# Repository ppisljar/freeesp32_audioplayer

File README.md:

# freeesp32_audioplayer

Open-source ESP32 audio playback board designed primarily as the hardware
platform for [**`freeesp32_ave`**](https://github.com/ppisljar/freeesp32_ave) —
audio-visual entrainment (AVE) firmware.

This repository contains the full **KiCad** project: schematic, PCB layout,
design rules, 3D models, datasheets, and helper scripts.

## Board renders

| Top | Bottom |
|---|---|
|  |  |

*KiCad 3D renders. Top: TRRS headphone jack, USB-C, microSD slot, XIAO ESP32-S3 module, LED/expansion pin headers. Bottom: speaker amplifier (APA2068), bulk capacitors, level-shifting resistors.*

## Board features

- **MCU module**: Seeed Studio **XIAO ESP32-S3** (Wi-Fi + BLE)
- **Headphone output**: Cirrus Logic **CS4344** stereo I²S DAC
- **Speaker output**: **APA2068** Class-D power amplifier
- **Storage**: microSD card slot for offline audio and timeline files
- **LED outputs**: configurable headers — works with NeoPixel (WS2812),
  DotStar (APA102), or direct PWM strips (the firmware picks the backend)

## Power

The board can be powered any of three ways. The 5 V rail feeds the speaker
amplifier (APA2068), and the XIAO's onboard LDO derives the 3.3 V rail
that feeds the DAC (CS4344) and the MCU itself.

| Source | Connector | Voltage | Notes |
|---|---|---|---|
| **USB-C** | XIAO ESP32-S3 onboard | 5 V (USB VBUS) | Also used for flashing firmware and the serial console. The default during development. |
| **External 5 V** | `J4` — JST PH 2-pin (`V+_EXT`) | 5 V regulated | For powering from a bench supply, wall adapter, or upstream USB-PD trigger. |
| **Li-ion battery** | `J5` — JST PH 2-pin (`BATTERY`) | 3.0 – 4.2 V | Connects to the XIAO's `BAT+` pin. The XIAO's built-in charger manages the cell when USB is also plugged in. |

### Battery-powered audio

A single Li-ion cell sits below the 5 V needed by the speaker amplifier,
so the board includes a **TPS61023 synchronous boost converter** (`U4`)
that lifts `BAT+` up to 5 V. Output is fed into the 5 V rail through a
Schottky diode (`D1`) so the boost output can't backfeed USB VBUS when
both USB and battery are connected.

This means the speaker output works on battery just as well as on USB —
no compromise.

### Combining sources — what's safe

| Combination | Safe? | Why |
|---|---|---|
| USB + battery | ✅ Yes | XIAO charges the cell; `D1` blocks the boost from feeding USB. |
| USB + external 5 V (`J4`) | ❌ **No — pick one** | Both feed the 5 V rail directly. Hot-swapping risks back-feeding the upstream supply. |
| External 5 V + battery | ✅ Yes | Same reasoning as USB + battery — `D1` isolates the boost. |

> **Tip**: if you intend to deploy the board untethered in a meditation
> session, leave USB unplugged once you've flashed the firmware. The
> XIAO's USB controller draws current even when the host is idle.

## Repository layout

```
main_board/
├── esp32audio.kicad_sch    # schematic
├── esp32audio.kicad_pcb    # PCB layout
├── esp32audio.kicad_pro    # KiCad project
├── 3dmodels/               # STEP models for enclosure design
├── datasheets/             # IC datasheets and reference schematics
├── analysis/               # generated reports (regenerable from source)
├── images/                 # 3D renders used in this README
├── outputs/                # gerbers, drill files, BOM, pick-and-place CSVs
└── *.py                    # helper scripts (netlist sync, freerouting…)
```

## Related projects

| Repo | Role |
|---|---|
| [`freeesp32_audioplayer`](https://github.com/ppisljar/freeesp32_audioplayer) | **This repo** — open hardware (KiCad) |
| [`freeesp32_ave`](https://github.com/ppisljar/freeesp32_ave) | AVE firmware that runs on this board |
| [`freeesp32_ave_generator`](https://github.com/ppisljar/freeesp32_ave_generator) | Web editor that generates session timelines for the firmware |

## Ordering the board

The `main_board/outputs/` directory contains everything a PCB fab needs:

| File / folder | Purpose |
|---|---|
| `outputs/Archive.zip` | Gerbers + drill file (KiCad standard layer naming) |
| `outputs/esp32audio.csv` | BOM with manufacturer part numbers (MPNs) |
| `outputs/esp32audio-*-pos.csv` | Pick-and-place coordinates (top / bottom / all) |

### PCBWay (recommended for assembly with non-LCSC parts)

1. Go to <https://www.pcbway.com/orderonline.aspx> and upload `outputs/Archive.zip`. The site auto-detects board size, layer count (2-layer), and finish.
2. Defaults are fine: **FR-4, 1.6 mm, HASL or ENIG, green soldermask, white silkscreen**.
3. For assembly: enable **PCB Assembly**, upload `esp32audio.csv` (BOM) and `esp32audio-top-pos.csv` + `esp32audio-bottom-pos.csv` (CPL). PCBWay sources parts by MPN globally — useful if any component is out of stock on LCSC.
4. Quoting + DFM review typically completes within 24 h; bare-board lead time ~3–5 days, assembled ~7–10 days.

### JLCPCB (cheaper for bare boards / parts available on LCSC)

1. Go to <https://cart.jlcpcb.com/quote> and upload `outputs/Archive.zip`.
2. Defaults are fine. JLCPCB's free options match what this design needs.
3. For assembly: enable **PCBA**, upload `esp32audio.csv` (BOM) and `esp32audio-all-pos.csv` (CPL). JLCPCB requires the parts to be in their LCSC catalog — verify MPN availability before ordering, and substitute equivalents in the BOM where needed.

### Bare-board only (any fab)

Just upload `outputs/Archive.zip` — the gerbers use KiCad's standard layer naming (`F_Cu`, `B_Cu`, `F_Mask`, `B_Mask`, `F_Paste`, `B_Paste`, `F_Silkscreen`, `B_Silkscreen`, `Edge_Cuts`) which every modern fab recognises.

### Regenerating outputs from source

If you edit the schematic or PCB, regenerate the manufacturing files from KiCad:

- **PCB → File → Fabrication Outputs → Gerbers…** (use `outputs/` as the output directory, then zip)
- **PCB → File → Fabrication Outputs → Drill Files…**
- **PCB → File → Fabrication Outputs → Component Placement…** (top + bottom CPL)
- **Schematic → Tools → Generate BOM…**

## Status

Hardware design in active development. See `main_board/project_plan.md` and
`main_board/lessons_learned.md` for design notes.

## License

TBD — open hardware license to be chosen (e.g. CERN-OHL-S 2.0).

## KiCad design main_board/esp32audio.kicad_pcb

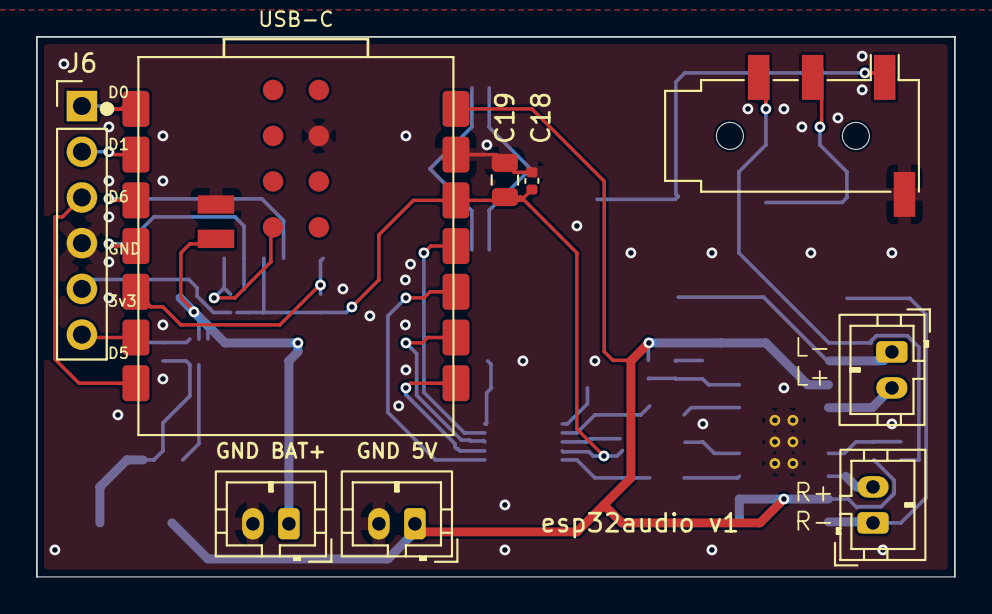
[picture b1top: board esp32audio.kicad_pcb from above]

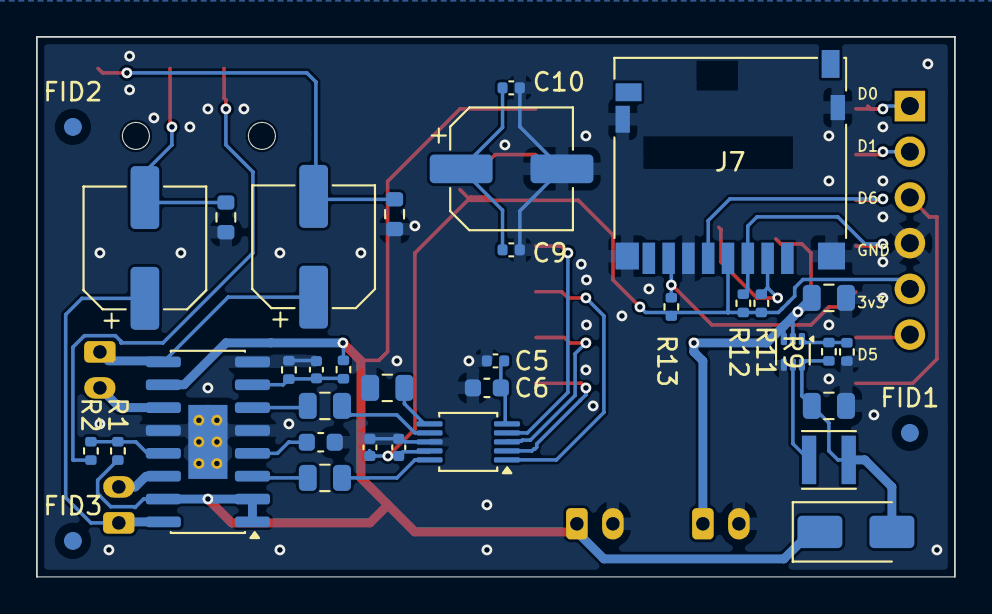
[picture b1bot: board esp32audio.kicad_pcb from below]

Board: 2 copper layers, 51.0 x 30.0 mm, 45 parts (36 on the bottom side), 35 nets.

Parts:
C2, C5, C9, C10, C15, C18: 0.1uF; C_0402_1005Metric
C3: 1uF; C_0402_1005Metric
C4, C16, C19: 10uF; C_0805_2012Metric
C6: 3.3uF; C_0603_1608Metric
C7, C8: 3.3uF; C_0805_2012Metric
C11: 100uF; CP_Elec_6.3x5.4
C12: 2.2uF; C_0603_1608Metric
C13, C14: 220uF; CP_Elec_6.3x5.4
C17: 22uF; C_0805_2012Metric
D1: SS14; D_SMA
FID1, FID2, FID3: Fiducial; Fiducial_1mm_Mask2mm
GND 5V: V+_EXT; JST_PH_B2B-PH-K_1x02_P2.00mm_Vertical
GND BAT+: BATTERY; JST_PH_B2B-PH-K_1x02_P2.00mm_Vertical
J1: PJ-320A; Jack_3.5mm_PJ320D_Horizontal
J2: L_SPKR; JST_PH_B2B-PH-K_1x02_P2.00mm_Vertical
J3: R_SPKR; JST_PH_B2B-PH-K_1x02_P2.00mm_Vertical
J6: GPIO_BREAKOUT; PinHeader_1x06_P2.54mm_Vertical
J7: microSD; microSD_HC_Hirose_DM3D-SF
L1: 4.7uH; L_Taiyo-Yuden_NR-30xx
R1, R2, R7: 100k; R_0402_1005Metric
R3, R4: 1k; R_0603_1608Metric
R8, R11, R12, R13: 10k; R_0402_1005Metric
R9: 365k; R_0402_1005Metric
R10: 49.9k; R_0402_1005Metric
U1: XIAO ESP32-S3; XIAO_ESP32-S3_SMD
U2: CS4344; TSSOP-10_3x3mm_P0.5mm
U3: APA2068; SOP-16-P_3.9x9.9mm_P1.27mm_EP2.18x4.12mm
U4: TPS61023DRLR; SOT-563

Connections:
/+3V3: C2.1, C3.1, C18.1, C19.1, J6.5, J7.4 (VDD), R11.1, R12.1, R13.1, U1.12 (3V3), U2.9 (VA)
/+5V: D1.1 (K), GND 5V.1, R1.1, R7.1, U1.14 (5V), U3.1 (~MUTE), U3.2 (~SHUTDOWN), U3.10 (VDD), U3.15 (VDD)
/AOUTL_AC: C7.2, U3.6 (LIN-)
/AOUTL_RAW: C7.1, U2.7 (AOUTL)
/AOUTR_AC: C8.2, U3.3 (RIN-)
/AOUTR_RAW: C8.1, U2.10 (AOUTR)
/BAT+: C16.1, GND BAT+.1, U1.15 (BAT+), U4.2 (EN), U4.3 (VIN)
/BOOST_OUT: C17.1, D1.2 (A), L1.2, R9.1, U4.6 (VOUT)
/BOOST_SW: L1.1, U4.5 (SW)
/BYPASS_C: C12.1, U3.4 (BYPASS)
/D0: J6.1, U1.1 (D0/GPIO1)
/D1_NET: J6.2, U1.2 (D1/GPIO2)
/D5_NET: J6.6, U1.6 (D5/GPIO6)
/D6_NET: J6.3, U1.7 (D6/GPIO43)
/FB_NET: R9.2, R10.1, U4.1 (FB)
/FILT_NET: C4.1, U2.6 (FILT+)
/GND: C2.2, C3.2, C4.2, C5.2, C6.2, C9.2, C10.2, C11.2, C12.2, C15.2, C16.2, C17.2, C18.2, C19.2, GND 5V.2, GND BAT+.2, J1.S, J6.4, J7.6 (VSS), J7.SH (SHIELD), R3.2, R4.2, R8.2, R10.2, U1.13 (GND), U1.16 (GND_BTM), U1.17 (GND_TP1), U2.8 (GND), U3.5 (GND), U3.8 (VOLMAX), U3.12 (GND), U3.17 (EP), U4.4 (GND)
/HP_L: C13.2, J1.T, R3.1
/HP_R: C14.2, R4.1
/I2S_BCLK: U1.8 (D7/GPIO44), U2.2 (~DEM/SCLK)
/I2S_DOUT: U1.10 (D9/GPIO8), U2.1 (SDIN)
/I2S_LRCK: U1.9 (D8/GPIO7), U2.3 (LRCK)
/I2S_MCLK: U1.11 (D10/GPIO9), U2.4 (MCLK)
/SD_CS: J7.2 (DAT3/CD), R11.2, U1.23 (USB_D-)
/SD_MISO: J7.7 (DAT0), R13.2, U1.5 (D4/GPIO5)
/SD_MOSI: J7.3 (CMD), R12.2, U1.4 (D3/GPIO4)
/SD_SCK: J7.5 (CLK), U1.3 (D2/GPIO3)
/SE_BTL: R1.2, R2.1, U3.13 (SE/~BTL)
/SPK_L_NEG: C13.1, J2.1, U3.9 (LOUT-)
/SPK_L_POS: J2.2, U3.11 (LOUT+)
/SPK_R_NEG: C14.1, J3.1, U3.16 (ROUT-)
/SPK_R_POS: J3.2, U3.14 (ROUT+)
/VOLUME_C: C15.1, R7.2, R8.1, U3.7 (VOLUME)
/VQ_NET: C5.1, C6.1, U2.5 (VQ)
unnamed: C9.1, C10.1, C11.1
